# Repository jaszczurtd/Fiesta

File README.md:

# Fiesta

[Polski](README.pl.md)

Firmware and electronics for a Ford Fiesta 1.8 diesel with a custom engine
combining 1.8D indirect-injection and 1.8TDDI direct-injection parts and a VP37 pump.
[JaszczurHAL](https://github.com/jaszczurtd/JaszczurHAL) supplies the hardware
interfaces and development tools. Author: Marcin "Jaszczur" Kielesiński.

The project is a proof of concept. The complete system has not been validated
as an integrated installation in a road-going car. ECU and VP37 trials use a
separate engine on a steel frame. Clocks and the ECU's supervisory functions
have been used in the car without VP37 actuation.

## Choose a task

| I want to... | Start here |
| --- | --- |
| Understand project readiness, limits and remaining work | [Project and hardware status](doc/STATUS.md) |
| Run the ECU and see measurements | [ECU first use](src/ECU/README.md) |
| View or compare saved measurements | [VP37 viewer](tools/vp37-viewer/README.md) |
| Build and upload firmware | [Builds and debugging](doc/BUILDING.md) |
| Understand modules and their connections | [Architecture](ARCHITECTURE.md) |
| Change settings or test outputs | [SerialConfigurator](src/SerialConfigurator/README.md) |

## Getting started

```bash
git clone --recurse-submodules https://github.com/jaszczurtd/Fiesta.git
cd Fiesta
```

Read [setup and firmware development](doc/BUILDING.md) before running
`runmefirst.sh`: it installs dependencies and clears module build directories.
After updating an existing checkout, use `./scripts/init_hal_submodule.sh`
to select the HAL revision recorded by Fiesta; it stops if HAL has local changes.

## Documentation

- [Architecture and communication](ARCHITECTURE.md)
- [Builds, upload and debugging](doc/BUILDING.md)
- [Host tests and CI](doc/TESTING.md)
- [VP37 measurement viewer](tools/vp37-viewer/README.md)
- [Updating JaszczurHAL](DEPENDENCIES.md)
- [Serial Configurator protocol](src/common/scDefinitions/PROTOCOL.md)
- [MISRA scope and review policy](MISRA.md)
- [Daily systemd build](src/ECU/scripts/systemd/README.md)
- [Gallery and bench photos](doc/GALLERY.md)

See [project status](doc/STATUS.md) for hardware compatibility and validation limits.

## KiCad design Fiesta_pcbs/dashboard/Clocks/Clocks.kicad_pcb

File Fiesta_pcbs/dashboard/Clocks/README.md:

# Clocks PCB

[Polski](README.pl.md)

The 0.1-review carrier is a first layout for assembly and enclosure review. It measures 70 ×
75 mm and carries the dashboard controller, CAN, GPS and thermocouple modules.

## Before connecting

- Use USB or vehicle power, never both at once. The circuit has no power-source arbitration. Vehicle feeds require fusing and transient protection.
- CAN and GPS assume 12 mm clearance from the carrier to the module underside; parts below them must stay under 8 mm. Confirm the fit with the actual sockets and enclosure.
- Check cooling of U3/U4/U8 and the specified regulator capacitor type and ESR. A regulator current rating does not establish the assembled board rating.
- Follow the connector numbers and module address settings in the assembly notes before using the firmware guide.

## Assembly and startup

The [assembly reference](ASSEMBLY.md) contains schematics, previews, connectors, component
selection and manufacturing requirements. It uses the KiCad project names and numbering.

After checking the hardware, follow the [firmware guide](../../../src/Clocks/README.md).

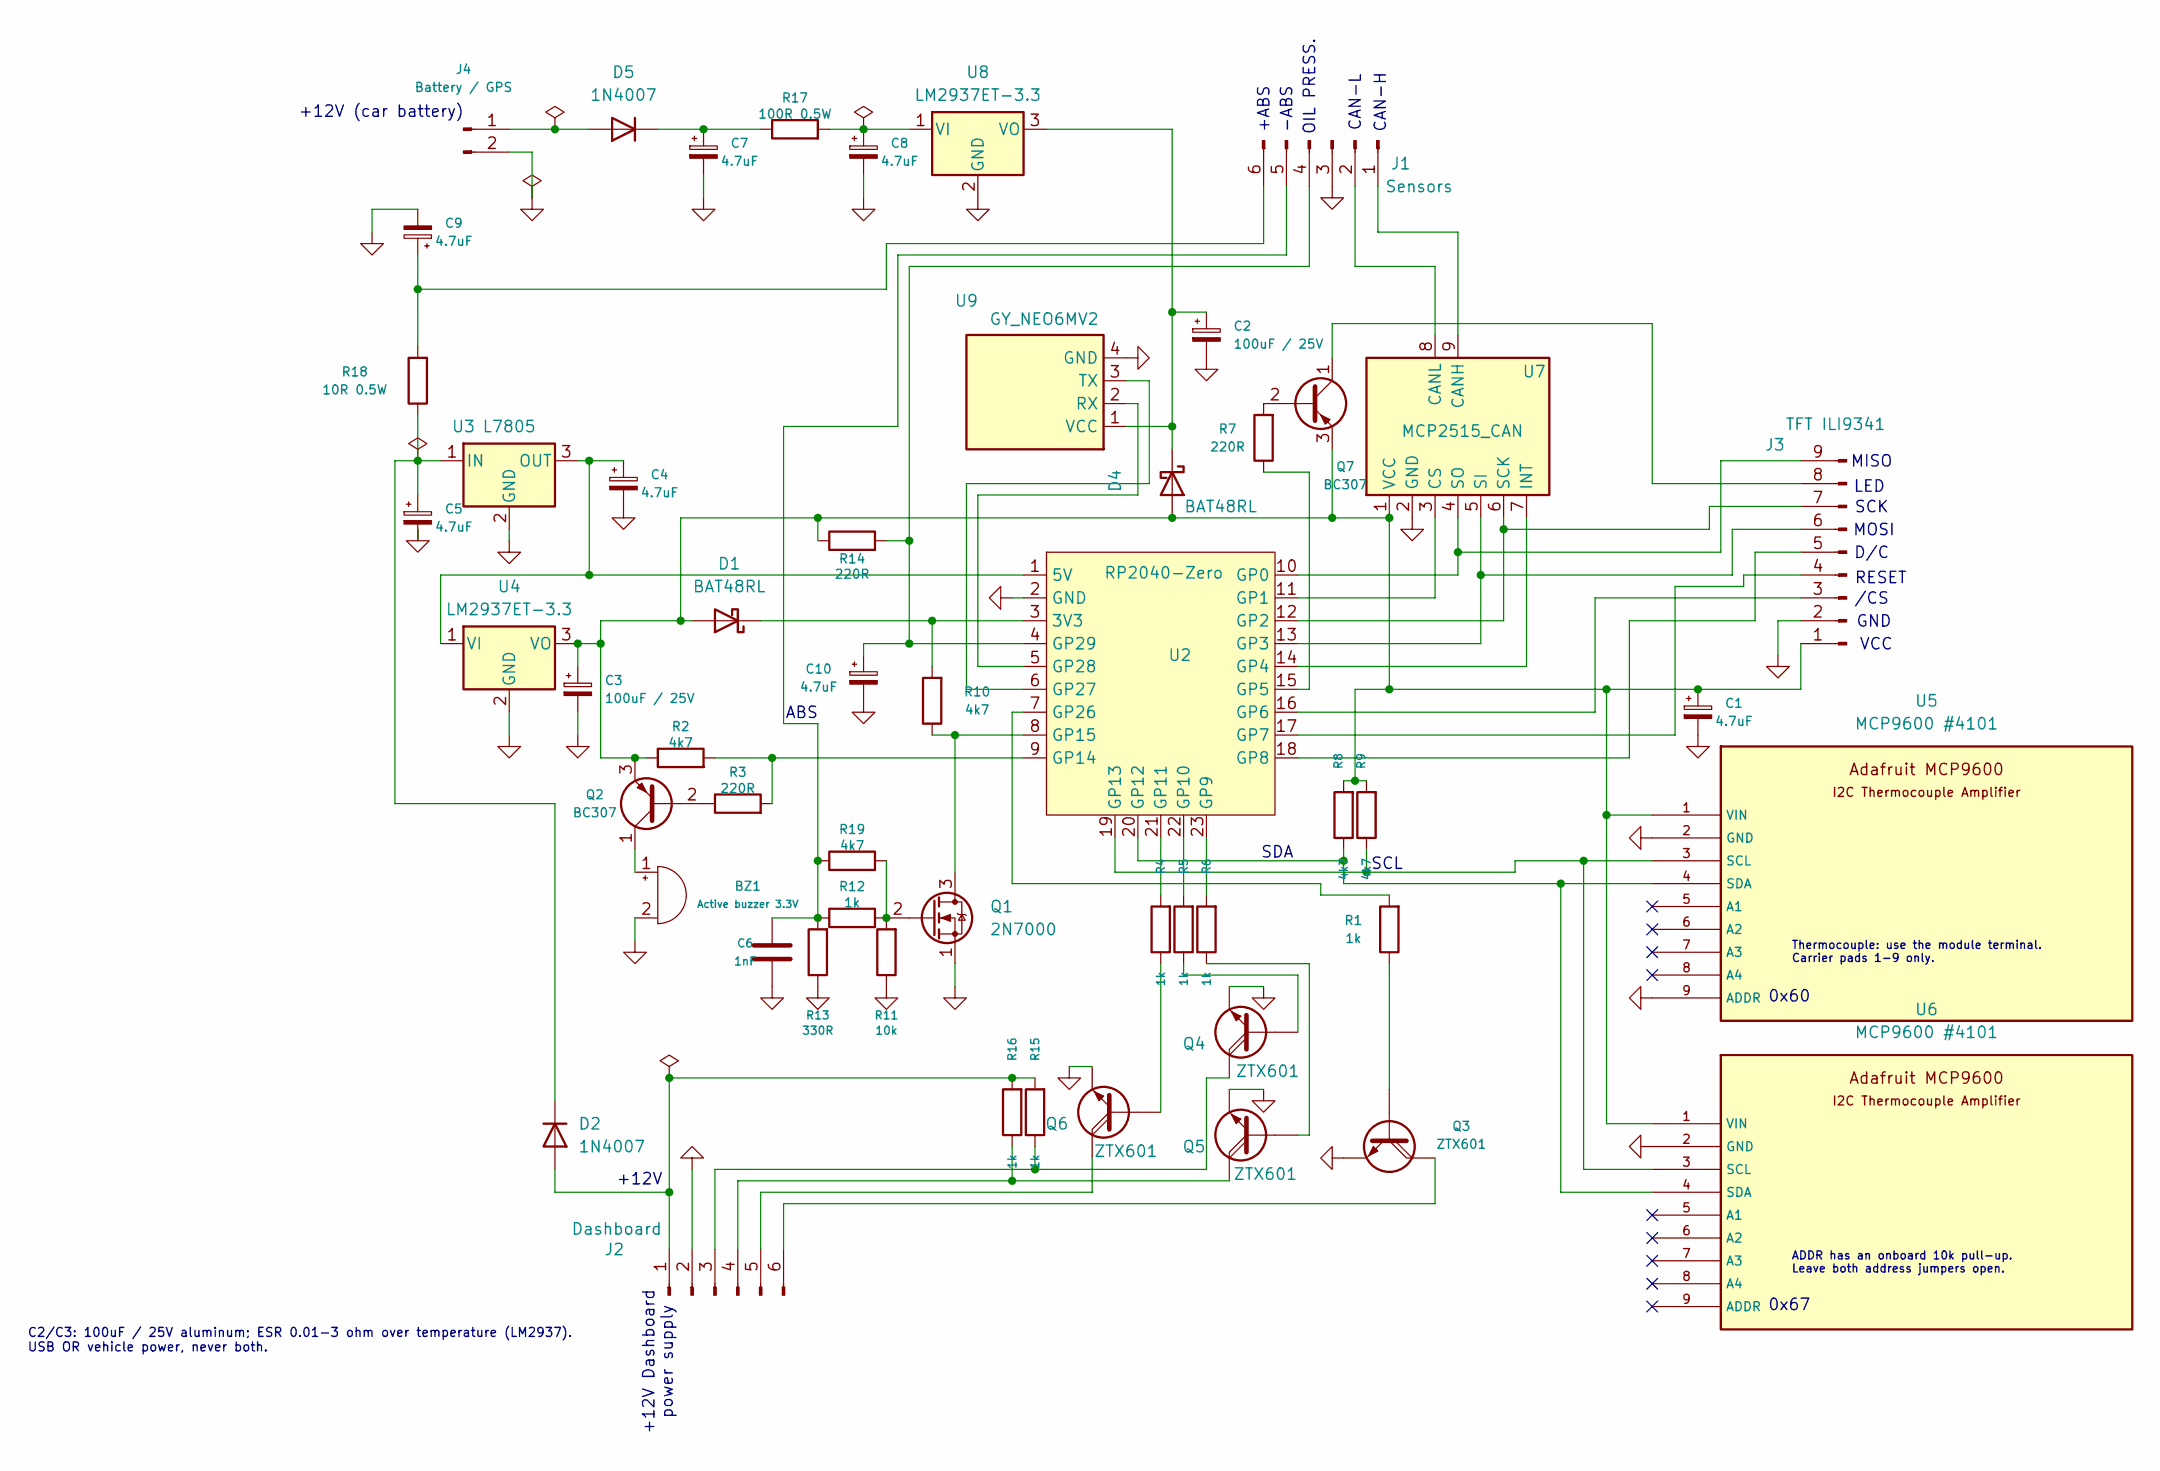
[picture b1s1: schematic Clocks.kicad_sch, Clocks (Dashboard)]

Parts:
BZ1: Active buzzer 3.3V; Buzzer_D11.5mm_H9mm_P8mm
C1, C4, C10: 4.7uF; CP_Radial_D6.3mm_P2.50mm; Voltage 25V minimum
C2, C3: 100uF / 25V; CP_Radial_D6.3mm_P2.50mm; Voltage 25V minimum
C5, C7, C8, C9: 4.7uF; CP_Radial_D6.3mm_P2.50mm; Voltage 50V minimum
C6: 1nF; C_0805_2012Metric; Voltage 25V minimum
D1, D4: BAT48RL; D_DO-35_SOD27_P7.62mm_Horizontal
D2, D5: 1N4007; D_DO-41_SOD81_P10.16mm_Horizontal
J1: Sensors; JST_XH_B6B-XH-A_1x06_P2.50mm_Vertical
J2: Dashboard; JST_XH_B6B-XH-A_1x06_P2.50mm_Vertical
J3: TFT ILI9341; JST_XH_B9B-XH-A_1x09_P2.50mm_Vertical
J4: Battery / GPS; JST_XH_B2B-XH-A_1x02_P2.50mm_Vertical
Q1: 2N7000; TO-92_Inline_Wide
Q2, Q7: BC307; TO-92_Inline_Wide
Q3, Q4, Q5, Q6: ZTX601; TO-92_Inline_Wide
R1, R4, R5, R6, R12: 1k; R_0805_2012Metric
R2, R8, R9, R10, R19: 4k7; R_0805_2012Metric
R3, R7, R14: 220R; R_0805_2012Metric
R11: 10k; R_0805_2012Metric
R13: 330R; R_0805_2012Metric
R15, R16: 1k; R_2512_6332Metric
R17: 100R 0.5W; R_2512_6332Metric
R18: 10R 0.5W; R_2512_6332Metric
U2: RP2040-Zero; RP2040-Zero_THT
U3: L7805; TO-220-3_Vertical
U4, U8: LM2937ET-3.3; TO-220-3_Vertical
U5, U6: MCP9600 #4101; Adafruit_MCP9600_4101_24.13x20.32mm
U7: MCP2515_CAN; MCP2515_40x27mm_Raised12mm
U9: GY_NEO6MV2; GY_NEO6MV2_25x35mm_Raised12mm

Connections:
GND: BZ1.2 (-), C1.2, C2.2, C3.2, C4.2, C5.2, C6.2, C7.2, C8.2, C9.2, C10.2, J1.3, J2.2, J3.2, J4.2, Q1.1 (S), Q3.1 (E), Q4.1 (E), Q5.1 (E), Q6.1 (E), R11.1, R13.1, U2.2 (GND), U3.2 (GND), U4.2 (GND), U5.2 (GND), U5.9 (ADDR), U6.2 (GND), U7.2 (GND), U8.2 (GND), U9.4 (GND)
unnamed: BZ1.1 (+), Q2.1 (C)
unnamed: C1.1, C3.1, D1.2 (A), D4.2 (A), J3.1, Q2.3 (E), Q7.3 (E), R2.1, R8.2, R9.2, R14.1, U4.3 (VO), U5.1 (VIN), U6.1 (VIN), U7.1 (VCC)
unnamed: D1.1 (K), R10.2, U2.3 (3V3)
unnamed: D2.2 (A), J2.1, R15.2, R16.2
unnamed: C5.1, D2.1 (K), R18.1, U3.1 (IN)
unnamed: C2.1, D4.1 (K), U8.3 (VO), U9.1 (VCC)
unnamed: D5.2 (A), J4.1
unnamed: C7.1, D5.1 (K), R17.1
unnamed: J1.1, U7.9 (CANH)
unnamed: J1.2, U7.8 (CANL)
unnamed: C10.1, J1.4, R14.2, U2.4 (GP29)
unnamed: C6.1, J1.5, R12.1, R13.2, R19.1
unnamed: C9.1, J1.6, R18.2
unnamed: J2.3, Q4.3 (C), R15.1
unnamed: J2.4, Q5.3 (C), R16.1
unnamed: J2.5, Q6.3 (C)
unnamed: J2.6, Q3.3 (C)
unnamed: J3.3, U2.16 (GP6)
unnamed: J3.4, U2.17 (GP7)
unnamed: J3.5, U2.18 (GP8)
unnamed: J3.6, U2.13 (GP3), U7.5 (SI)
unnamed: J3.7, U2.12 (GP2), U7.6 (SCK)
unnamed: J3.8, Q7.1 (C)
unnamed: J3.9, U2.10 (GP0), U7.4 (SO)
unnamed: Q1.3 (D), R10.1, U2.8 (GP15)
unnamed: Q1.2 (G), R11.2, R12.2, R19.2
unnamed: Q2.2 (B), R3.1
unnamed: Q3.2 (B), R1.1
unnamed: Q4.2 (B), R5.1
unnamed: Q5.2 (B), R6.1
unnamed: Q6.2 (B), R4.1
unnamed: Q7.2 (B), R7.2
unnamed: C4.1, U2.1 (5V), U3.3 (OUT), U4.1 (VI)
unnamed: U2.11 (GP1), U7.3 (CS)
unnamed: U2.14 (GP4), U7.7 (INT)
unnamed: R7.1, U2.15 (GP5)
unnamed: R6.2, U2.23 (GP9)
unnamed: R5.2, U2.22 (GP10)
unnamed: R4.2, U2.21 (GP11)
unnamed: R8.1, U2.20 (GP12), U5.4 (SDA), U6.4 (SDA)
unnamed: R9.1, U2.19 (GP13), U5.3 (SCL), U6.3 (SCL)
unnamed: R2.2, R3.2, U2.9 (GP14)
unnamed: R1.2, U2.7 (GP26)
unnamed: U2.6 (GP27), U9.3 (TX)
unnamed: U2.5 (GP28), U9.2 (RX)
unnamed: C8.1, R17.2, U8.1 (VI)

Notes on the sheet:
CAN-H
+ABS
+12V (car battery)
+12V Dashboard power supply
LED
MOSI
SCL
/CS
OIL PRESS.
MISO
D/C
SCK
SDA
CAN-L
-ABS
+12V
VCC
GND
RESET
0x60
0x67
ABS
Thermocouple: use the module terminal. Carrier pads 1-9 only.
ADDR has an onboard 10k pull-up. Leave both address jumpers open.
C2/C3: 100uF / 25V aluminum; ESR 0.01-3 ohm over temperature (LM2937). USB OR vehicle power, never both.

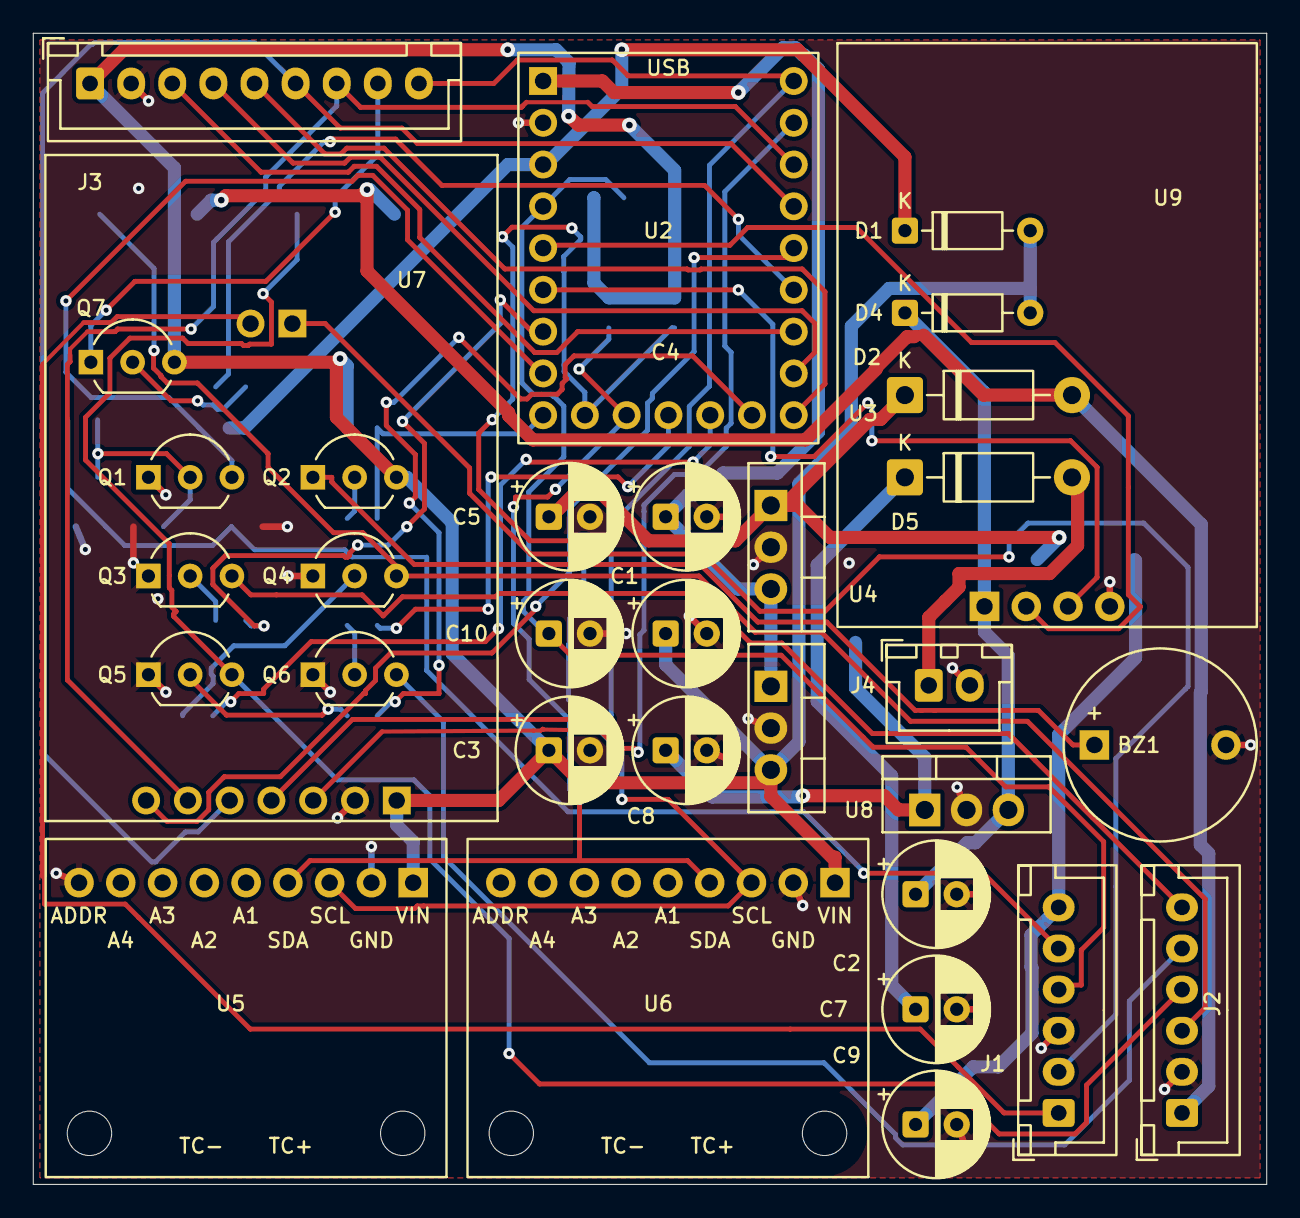
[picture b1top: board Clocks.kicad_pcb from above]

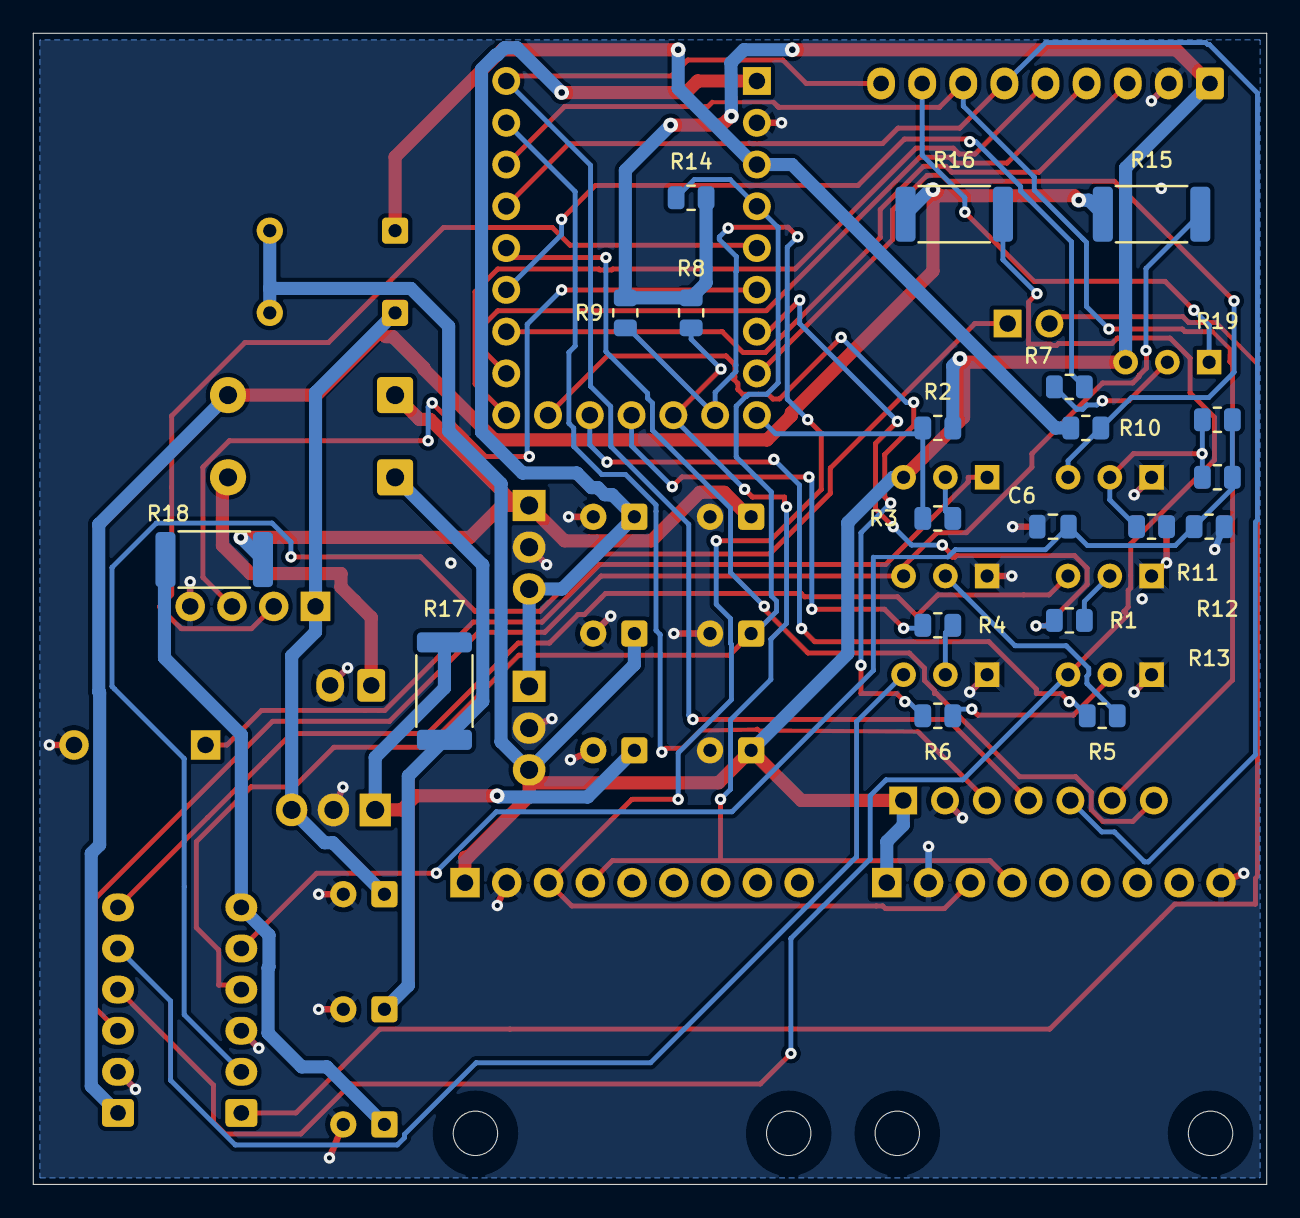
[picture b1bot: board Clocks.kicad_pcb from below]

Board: 2 copper layers, 75.0 x 70.0 mm, 53 parts (20 on the bottom side), 47 nets.

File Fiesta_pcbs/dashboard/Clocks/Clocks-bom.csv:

"Reference","Value","Footprint","Voltage","Power","Selection","Description","Datasheet"
"BZ1","Active buzzer 3.3V","Clocks:Buzzer_D11.5mm_H9mm_P8mm","","","","Active DC buzzer; measured diameter 11.5mm, height 9mm, lead spacing 8mm; pin 1 positive","~"
"C1","4.7uF","Capacitor_THT:CP_Radial_D6.3mm_P2.50mm","25V minimum","","","Polarized capacitor, small symbol","~"
"C2","100uF / 25V","Capacitor_THT:CP_Radial_D6.3mm_P2.50mm","25V minimum","","Aluminum electrolytic, -40..105C; C >= 10uF and ESR 0.01..3 ohm over operating temperature","Polarized capacitor, small symbol","~"
"C3","100uF / 25V","Capacitor_THT:CP_Radial_D6.3mm_P2.50mm","25V minimum","","Aluminum electrolytic, -40..105C; C >= 10uF and ESR 0.01..3 ohm over operating temperature","Polarized capacitor, small symbol","~"
"C4","4.7uF","Capacitor_THT:CP_Radial_D6.3mm_P2.50mm","25V minimum","","","Polarized capacitor, small symbol","~"
"C5","4.7uF","Capacitor_THT:CP_Radial_D6.3mm_P2.50mm","50V minimum","","","Polarized capacitor, small symbol","~"
"C6","1nF","Capacitor_SMD:C_0805_2012Metric","25V minimum","","","Unpolarized capacitor","~"
"C7","4.7uF","Capacitor_THT:CP_Radial_D6.3mm_P2.50mm","50V minimum","","","Polarized capacitor, small symbol","~"
"C8","4.7uF","Capacitor_THT:CP_Radial_D6.3mm_P2.50mm","50V minimum","","","Polarized capacitor, small symbol","~"
"C9","4.7uF","Capacitor_THT:CP_Radial_D6.3mm_P2.50mm","50V minimum","","","Polarized capacitor, small symbol","~"
"C10","4.7uF","Capacitor_THT:CP_Radial_D6.3mm_P2.50mm","25V minimum","","","Polarized capacitor, small symbol","~"
"D1","BAT48RL","Diode_THT:D_DO-35_SOD27_P7.62mm_Horizontal","","","","40V 0.35A Small Signal Schottky Diode, DO-35","www.st.com/resource/en/datasheet/bat48.pdf"
"D2","1N4007","Diode_THT:D_DO-41_SOD81_P10.16mm_Horizontal","","","","1000V 1A General Purpose Rectifier Diode, DO-41","http://www.vishay.com/docs/88503/1n4001.pdf"
"D4","BAT48RL","Diode_THT:D_DO-35_SOD27_P7.62mm_Horizontal","","","","40V 0.35A Small Signal Schottky Diode, DO-35","www.st.com/resource/en/datasheet/bat48.pdf"
"D5","1N4007","Diode_THT:D_DO-41_SOD81_P10.16mm_Horizontal","","","","1000V 1A General Purpose Rectifier Diode, DO-41","http://www.vishay.com/docs/88503/1n4001.pdf"
"J1","Sensors","Connector_JST:JST_XH_B6B-XH-A_1x06_P2.50mm_Vertical","","","","Generic connector, single row, 01x06, script generated","~"
"J2","Dashboard","Connector_JST:JST_XH_B6B-XH-A_1x06_P2.50mm_Vertical","","","","Generic connector, single row, 01x06, script generated","~"
"J3","TFT ILI9341","Connector_JST:JST_XH_B9B-XH-A_1x09_P2.50mm_Vertical","","","","Generic connector, single row, 01x09, script generated","~"
"J4","Battery / GPS","Connector_JST:JST_XH_B2B-XH-A_1x02_P2.50mm_Vertical","","","","Generic connector, single row, 01x02, script generated","~"
"Q1","2N7000","Package_TO_SOT_THT:TO-92_Inline_Wide","","","","0.2A Id, 200V Vds, N-Channel MOSFET, 2.6V Logic Level, TO-92","https://www.vishay.com/docs/70226/70226.pdf"
"Q2","BC307","Package_TO_SOT_THT:TO-92_Inline_Wide","","","","100mA Ic, 45V Vce, Epitaxial Silicon PNP Transistor, TO-92","http://www.onsemi.com/pub_link/Collateral/BC307-D.PDF"
"Q3","ZTX601","Package_TO_SOT_THT:TO-92_Inline_Wide","","","","NPN Darlington  bipolar junction transistor","https://www.diodes.com/datasheet/download/ZTX601.pdf"
"Q4","ZTX601","Package_TO_SOT_THT:TO-92_Inline_Wide","","","","NPN Darlington  bipolar junction transistor","https://www.diodes.com/datasheet/download/ZTX601.pdf"
"Q5","ZTX601","Package_TO_SOT_THT:TO-92_Inline_Wide","","","","NPN Darlington  bipolar junction transistor","https://www.diodes.com/datasheet/download/ZTX601.pdf"
"Q6","ZTX601","Package_TO_SOT_THT:TO-92_Inline_Wide","","","","NPN Darlington  bipolar junction transistor","https://www.diodes.com/datasheet/download/ZTX601.pdf"
"Q7","BC307","Package_TO_SOT_THT:TO-92_Inline_Wide","","","","100mA Ic, 45V Vce, Epitaxial Silicon PNP Transistor, TO-92","http://www.onsemi.com/pub_link/Collateral/BC307-D.PDF"
"R1","1k","Resistor_SMD:R_0805_2012Metric","","","","Resistor","~"
"R2","4k7","Resistor_SMD:R_0805_2012Metric","","","","Resistor","~"
"R3","220R","Resistor_SMD:R_0805_2012Metric","","","","Resistor","~"
"R4","1k","Resistor_SMD:R_0805_2012Metric","","","","Resistor","~"
"R5","1k","Resistor_SMD:R_0805_2012Metric","","","","Resistor","~"
"R6","1k","Resistor_SMD:R_0805_2012Metric","","","","Resistor","~"
"R7","220R","Resistor_SMD:R_0805_2012Metric","","","","Resistor","~"
"R8","4k7","Resistor_SMD:R_0805_2012Metric","","","","Resistor","~"
"R9","4k7","Resistor_SMD:R_0805_2012Metric","","","","Resistor","~"
"R10","4k7","Resistor_SMD:R_0805_2012Metric","","","","Resistor","~"
"R11","10k","Resistor_SMD:R_0805_2012Metric","","","","Resistor","~"
"R12","1k","Resistor_SMD:R_0805_2012Metric","","","","Resistor","~"
"R13","330R","Resistor_SMD:R_0805_2012Metric","","","","Resistor","~"
"R14","220R","Resistor_SMD:R_0805_2012Metric","","","","Resistor","~"
"R15","1k","Resistor_SMD:R_2512_6332Metric","","0.5W minimum","","Resistor","~"
"R16","1k","Resistor_SMD:R_2512_6332Metric","","0.5W minimum","","Resistor","~"
"R17","100R 0.5W","Resistor_SMD:R_2512_6332Metric","","0.5W minimum","","Resistor","~"
"R18","10R 0.5W","Resistor_SMD:R_2512_6332Metric","","0.5W minimum","","Resistor","~"
"R19","4k7","Resistor_SMD:R_0805_2012Metric","","","","Resistor","~"
"U2","RP2040-Zero","Adjustometer:RP2040-Zero_THT","","","","",""
"U3","L7805","Package_TO_SOT_THT:TO-220-3_Vertical","","","","Positive 1.5A 35V Linear Regulator, Fixed Output 5V, TO-220/TO-263/TO-252","http://www.st.com/content/ccc/resource/technical/document/da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"
"U4","LM2937ET-3.3","Package_TO_SOT_THT:TO-220-3_Vertical","","","","500mA fixed 3.3V LDO; TO-220, 1=IN, 2=GND/tab, 3=OUT","https://www.ti.com/lit/ds/symlink/lm2937.pdf"
"U5","MCP9600 #4101","Clocks:Adafruit_MCP9600_4101_24.13x20.32mm","","","","Adafruit MCP9600 I2C Thermocouple Amplifier breakout","https://github.com/adafruit/Adafruit-MCP9600-PCB"
"U6","MCP9600 #4101","Clocks:Adafruit_MCP9600_4101_24.13x20.32mm","","","","Adafruit MCP9600 I2C Thermocouple Amplifier breakout","https://github.com/adafruit/Adafruit-MCP9600-PCB"
"U7","MCP2515_CAN","Clocks:MCP2515_40x27mm_Raised12mm","","","","",""
"U8","LM2937ET-3.3","Package_TO_SOT_THT:TO-220-3_Vertical","","","","500mA fixed 3.3V LDO; TO-220, 1=IN, 2=GND/tab, 3=OUT","https://www.ti.com/lit/ds/symlink/lm2937.pdf"
"U9","GY_NEO6MV2","Clocks:GY_NEO6MV2_25x35mm_Raised12mm","","","","",""

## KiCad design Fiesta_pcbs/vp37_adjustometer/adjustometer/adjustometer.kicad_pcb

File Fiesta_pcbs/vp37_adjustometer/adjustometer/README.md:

# Adjustometer PCB

[Polski](README.pl.md)

A 45 × 36 mm prototype position-sensor carrier for VP37, with RP2040-Zero and a Hartley
oscillator. The firmware guide explains baseline acquisition and feedback validity.

## Before connecting

- Supply both regulated 5 V and 12 V with a common ground. U1 supplies only the 8 V oscillator rail.
- Disconnect external 5 V before powering RP2040-Zero through USB: USB VBUS and its 5 V header share a net.
- J1 pins 1-5 map to pump harness pins 1, 2, 3, 4 and 7. J2 pins 1-5 are 5 V, GND, SDA, SCL and 12 V. Confirm orientation in the assembly notes.
- Reset with the actuator drive off and the mechanism settled. Wait for a valid baseline, then reset the ECU.

## Assembly and startup

The [assembly reference](ASSEMBLY.md) contains schematics, previews, connectors, component
selection and manufacturing requirements. It uses the KiCad project names and numbering.

After checking the hardware, follow the [firmware guide](../../../src/Adjustometer/README.md).

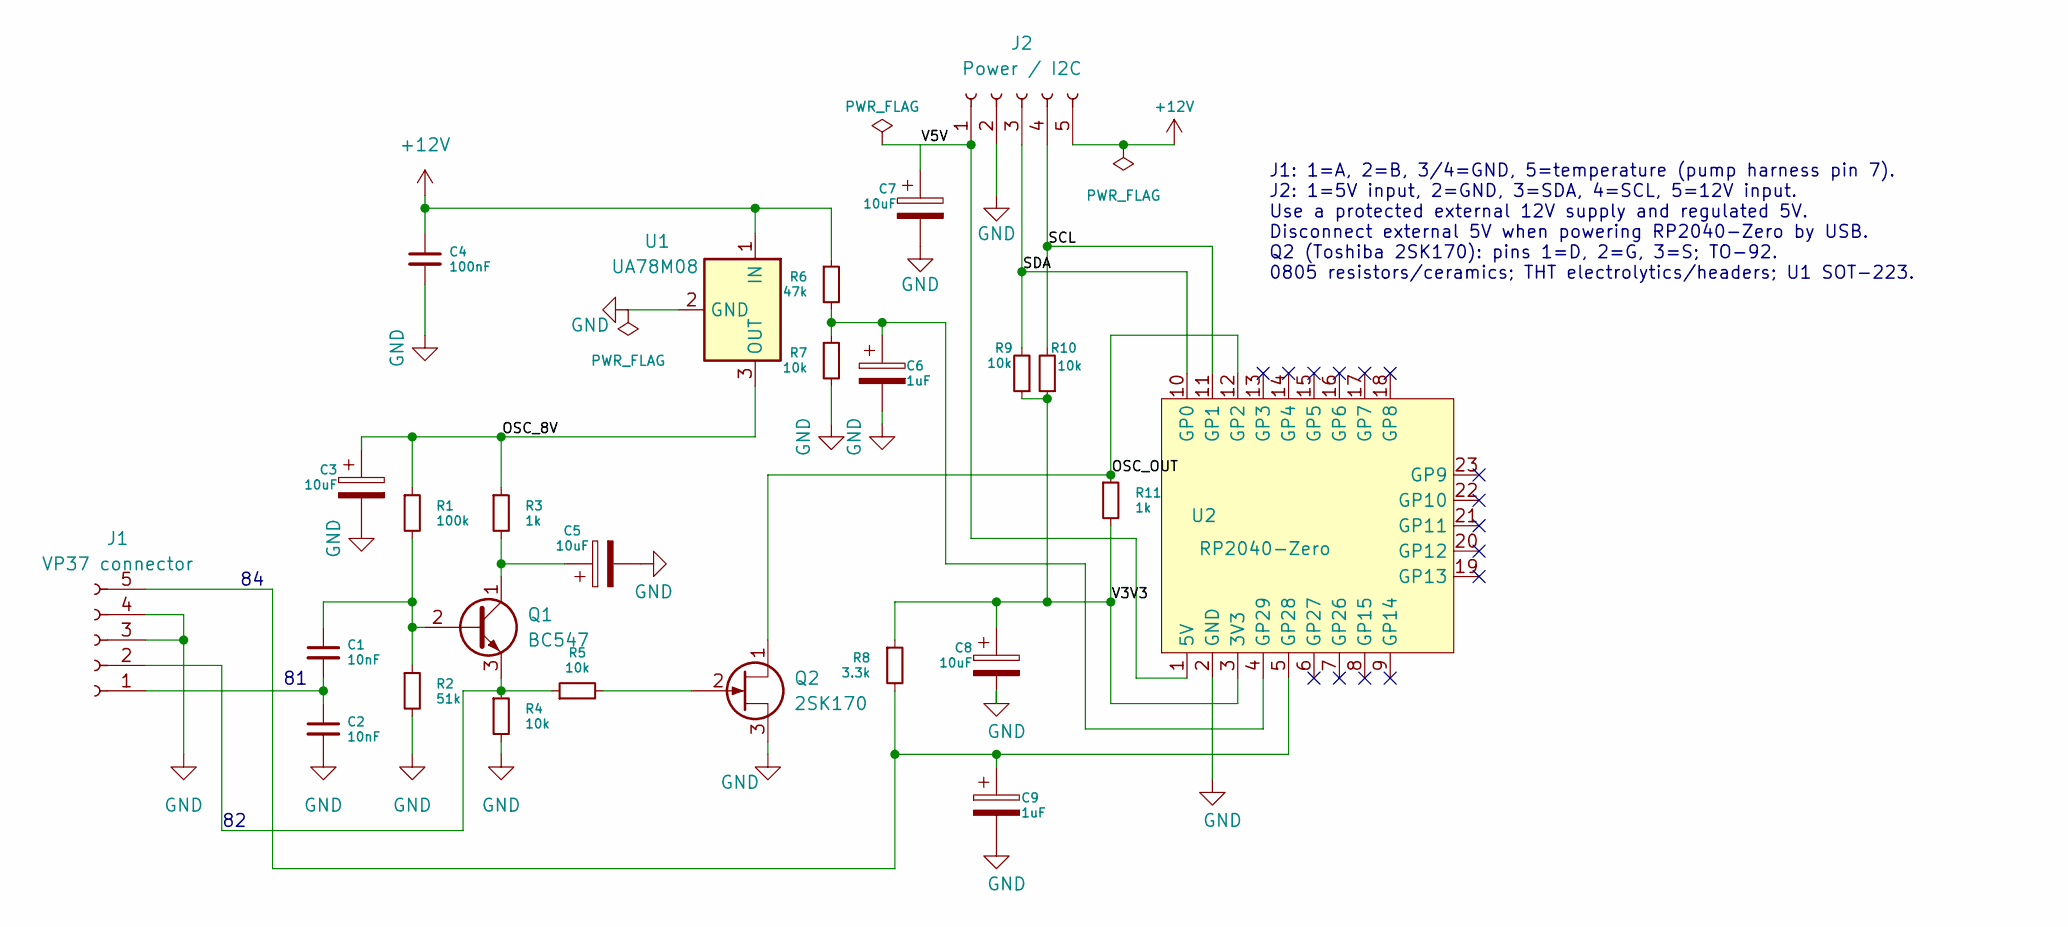
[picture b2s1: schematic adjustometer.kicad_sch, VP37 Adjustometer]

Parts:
C1, C2: 10nF; C_0805_2012Metric
C3, C5, C7, C8: 10uF; CP_Radial_D5.0mm_P2.00mm
C4: 100nF; C_0805_2012Metric
C6, C9: 1uF; CP_Radial_D5.0mm_P2.00mm
J1: VP37 connector; PinHeader_1x05_P2.54mm_Vertical
J2: Power / I2C; PinHeader_1x05_P2.54mm_Vertical
Q1: BC547; TO-92_Inline
Q2: 2SK170; TO-92_Inline
R1: 100k; R_0805_2012Metric
R2: 51k; R_0805_2012Metric
R3, R11: 1k; R_0805_2012Metric
R4, R5, R7, R9, R10: 10k; R_0805_2012Metric
R6: 47k; R_0805_2012Metric
R8: 3.3k; R_0805_2012Metric
U1: UA78M08; SOT-223-3_TabPin2
U2: RP2040-Zero; RP2040-Zero_THT

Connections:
+12V: C4.1, J2.5, R6.1, U1.1 (IN)
/OSC_8V: C3.1, R1.1, R3.1, U1.3 (OUT)
/OSC_OUT: Q2.1 (D), R11.1, U2.12 (GP2)
/SCL: J2.4, R10.2, U2.11 (GP1)
/SDA: J2.3, R9.2, U2.10 (GP0)
/V3V3: C8.1, R8.1, R9.1, R10.1, R11.2, U2.3 (3V3)
/V5V: C7.1, J2.1, U2.1 (5V)
GND: C2.2, C3.2, C4.2, C5.2, C6.2, C7.2, C8.2, C9.2, J1.3, J1.4, J2.2, Q2.3 (S), R2.2, R4.2, R7.2, U1.2 (GND), U2.2 (GND)
unnamed: C1.2, C2.1, J1.1
unnamed: J1.2, Q1.3 (E), R4.1, R5.1
unnamed: C9.1, J1.5, R8.2, U2.5 (GP28)
unnamed: C1.1, Q1.2 (B), R1.2, R2.1
unnamed: C5.1, Q1.1 (C), R3.2
unnamed: Q2.2 (G), R5.2
unnamed: C6.1, R6.2, R7.1, U2.4 (GP29)

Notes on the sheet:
J1: 1=A, 2=B, 3/4=GND, 5=temperature (pump harness pin 7). J2: 1=5V input, 2=GND, 3=SDA, 4=SCL, 5=12V input. Use a protected external 12V supply and regulated 5V. Disconnect external 5V when powering RP2040-Zero by USB. Q2 (Toshiba 2SK170): pins 1=D, 2=G, 3=S; TO-92. 0805 resistors/ceramics; THT el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

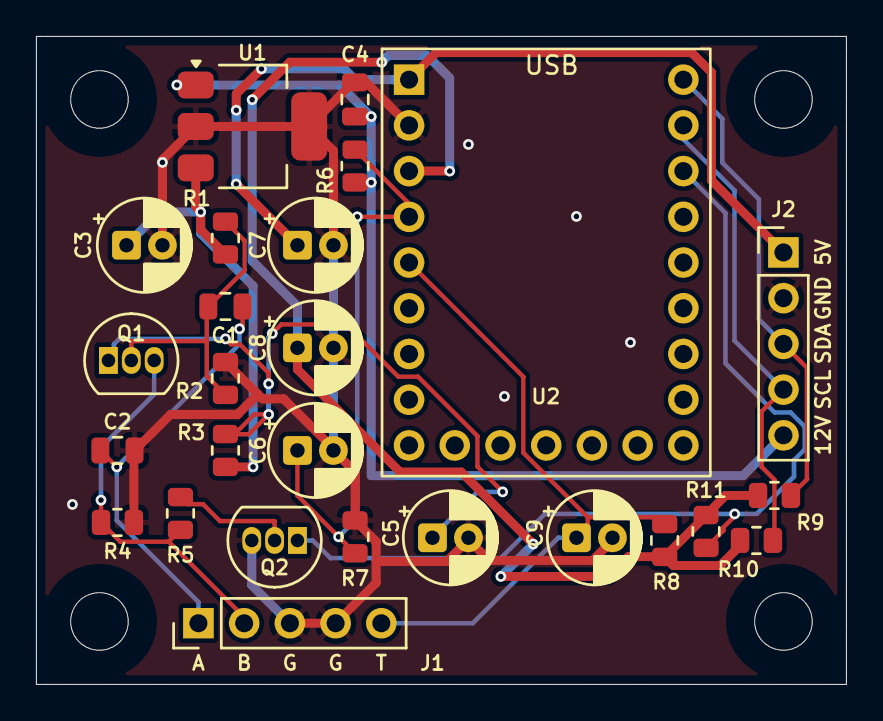
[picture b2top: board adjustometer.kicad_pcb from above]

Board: 2 copper layers, 45.0 x 36.0 mm, 30 parts (0 on the bottom side), 15 nets.

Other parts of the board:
H1, H2, H3, H4: M3; MountingHole_3.2mm_M3

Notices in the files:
Fiesta_pcbs/ecu/ECU/ECU.kicad_pcb:
Fiesta VP37 ECU (c) 2026
